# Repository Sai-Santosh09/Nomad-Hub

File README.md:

# NomadHub

NomadHub is a compact travel-inspired USB hub PCB designed in **KiCad**. It provides reliable USB connectivity through one USB Type-C upstream port, two USB Type-C downstream ports, and two USB Type-A downstream ports using the SL2.1S USB 2.0 Hub Controller.

## Features

- Compact travel-friendly PCB
- USB Type-C upstream port
- 2 × USB Type-C downstream ports
- 2 × USB Type-A downstream ports
- SL2.1S USB 2.0 Hub Controller
- 2-layer PCB design
- USB 2.0 compliant routing
- Gerber files included

## Images

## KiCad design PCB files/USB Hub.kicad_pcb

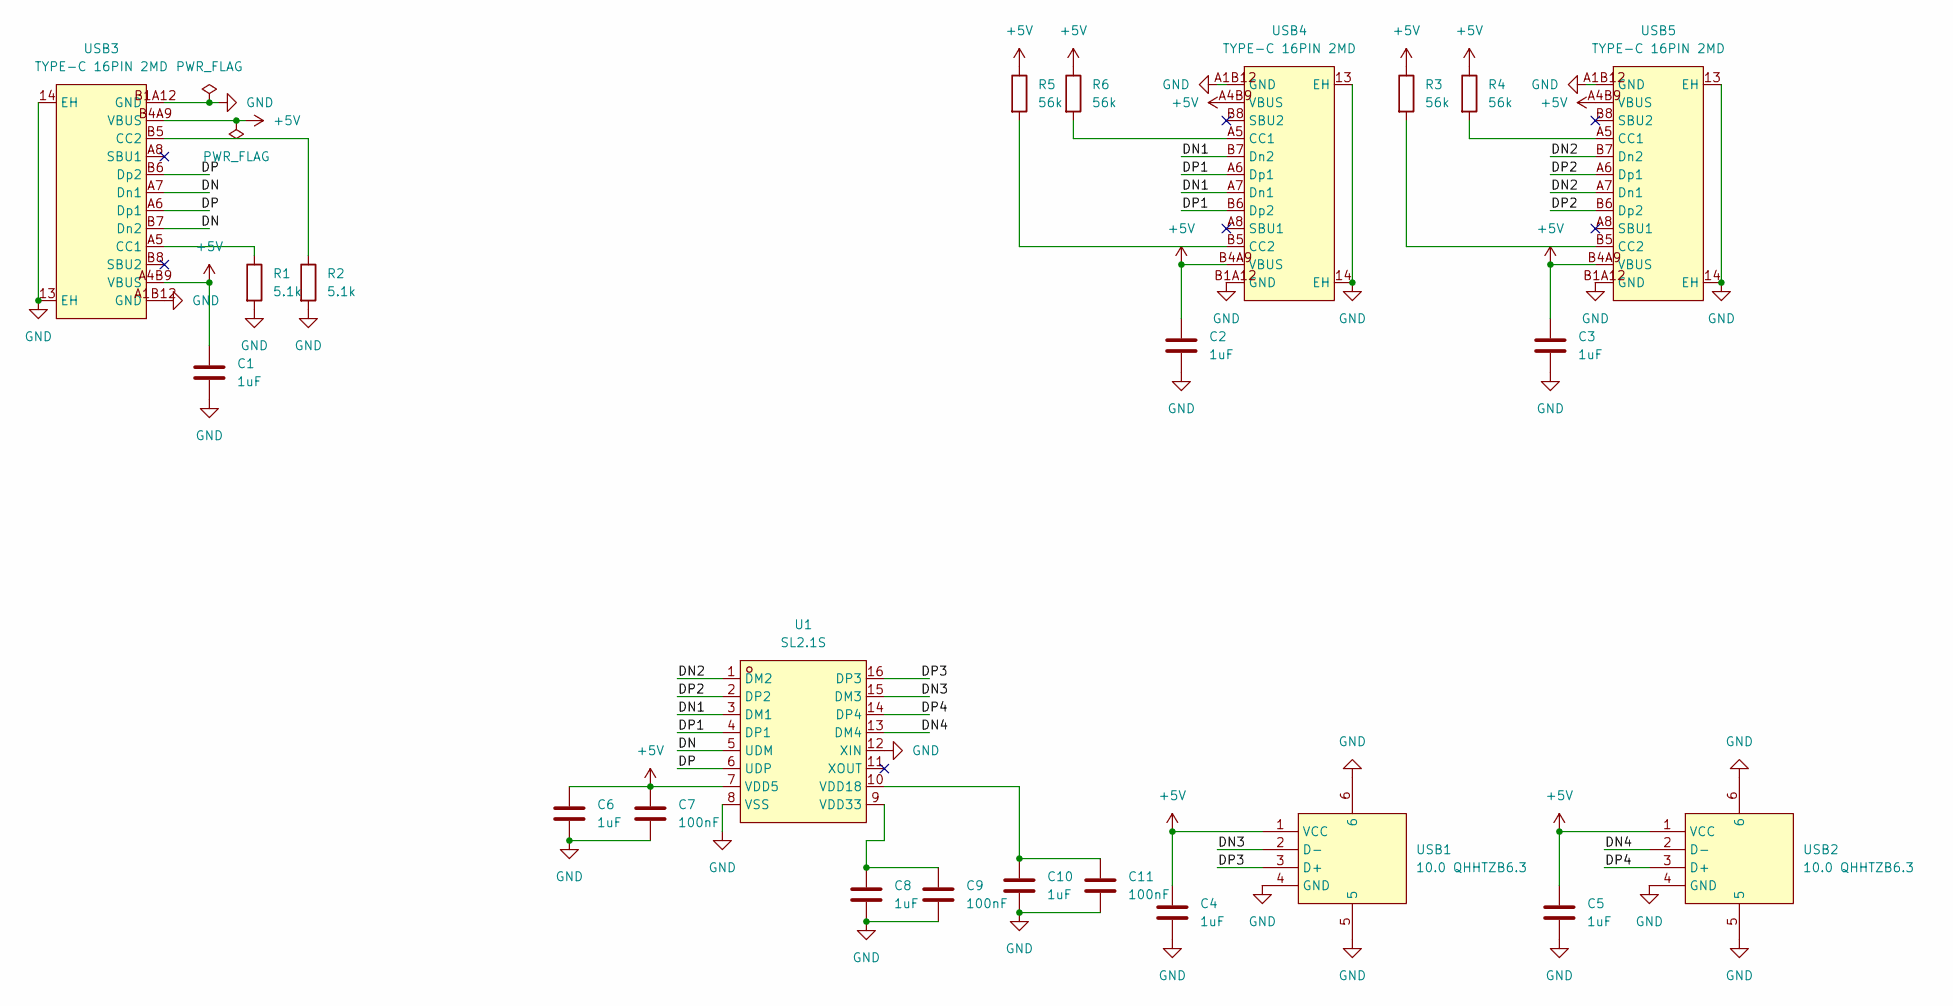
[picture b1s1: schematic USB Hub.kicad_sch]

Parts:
C1, C2, C3, C4, C5, C6, C8, C10: 1uF; C_0603_1608Metric
C7, C9, C11: 100nF; C_0603_1608Metric
R1, R2: 5.1k; R_0603_1608Metric
R3, R4, R5, R6: 56k; R_0603_1608Metric
U1: SL2.1S; SSOP-16_L4.6-W2.6-P0.53-LS4.0-BL; MPN SL2.1s; LCSC Part C2684433
USB1, USB2: 10.0 QHHTZB6.3; USB-A-TH_10.0QHHTZB6.3; MPN 10.0 QHHTZB6.3; LCSC Part C668591
USB3, USB4, USB5: TYPE-C 16PIN 2MD; USB-C-SMD_TYPE-C-16PIN-2MD-073; MPN TYPE-C 16PIN 2MD(073); LCSC Part C2765186

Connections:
+5V: C1.1, C2.1, C3.1, C4.1, C5.1, C6.1, C7.1, R3.1, R4.1, R5.1, R6.1, U1.7 (VDD5), USB1.1 (VCC), USB2.1 (VCC), USB3.A4B9 (VBUS), USB3.B4A9 (VBUS), USB4.A4B9 (VBUS), USB4.B4A9 (VBUS), USB5.A4B9 (VBUS), USB5.B4A9 (VBUS)
/DN: U1.5 (UDM), USB3.A7 (Dn1), USB3.B7 (Dn2)
/DN1: U1.3 (DM1), USB4.A7 (Dn1), USB4.B7 (Dn2)
/DN2: U1.1 (DM2), USB5.A7 (Dn1), USB5.B7 (Dn2)
/DN3: U1.15 (DM3), USB1.2 (D-)
/DN4: U1.13 (DM4), USB2.2 (D-)
/DP: U1.6 (UDP), USB3.A6 (Dp1), USB3.B6 (Dp2)
/DP1: U1.4 (DP1), USB4.A6 (Dp1), USB4.B6 (Dp2)
/DP2: U1.2 (DP2), USB5.A6 (Dp1), USB5.B6 (Dp2)
/DP3: U1.16 (DP3), USB1.3 (D+)
/DP4: U1.14 (DP4), USB2.3 (D+)
GND: C1.2, C2.2, C3.2, C4.2, C5.2, C6.2, C7.2, C8.2, C9.2, C10.2, C11.2, R1.2, R2.2, U1.8 (VSS), U1.12 (XIN), USB1.4 (GND), USB1.5, USB1.6, USB2.4 (GND), USB2.5, USB2.6, USB3.13 (EH), USB3.14 (EH), USB3.A1B12 (GND), USB3.B1A12 (GND), USB4.13 (EH), USB4.14 (EH), USB4.A1B12 (GND), USB4.B1A12 (GND), USB5.13 (EH), USB5.14 (EH), USB5.A1B12 (GND), USB5.B1A12 (GND)
unnamed: C10.1, C11.1, U1.10 (VDD18)
unnamed: C8.1, C9.1, U1.9 (VDD33)
unnamed: R1.1, USB3.A5 (CC1)
unnamed: R2.1, USB3.B5 (CC2)
unnamed: R6.2, USB4.A5 (CC1)
unnamed: R5.2, USB4.B5 (CC2)
unnamed: R4.2, USB5.A5 (CC1)
unnamed: R3.2, USB5.B5 (CC2)

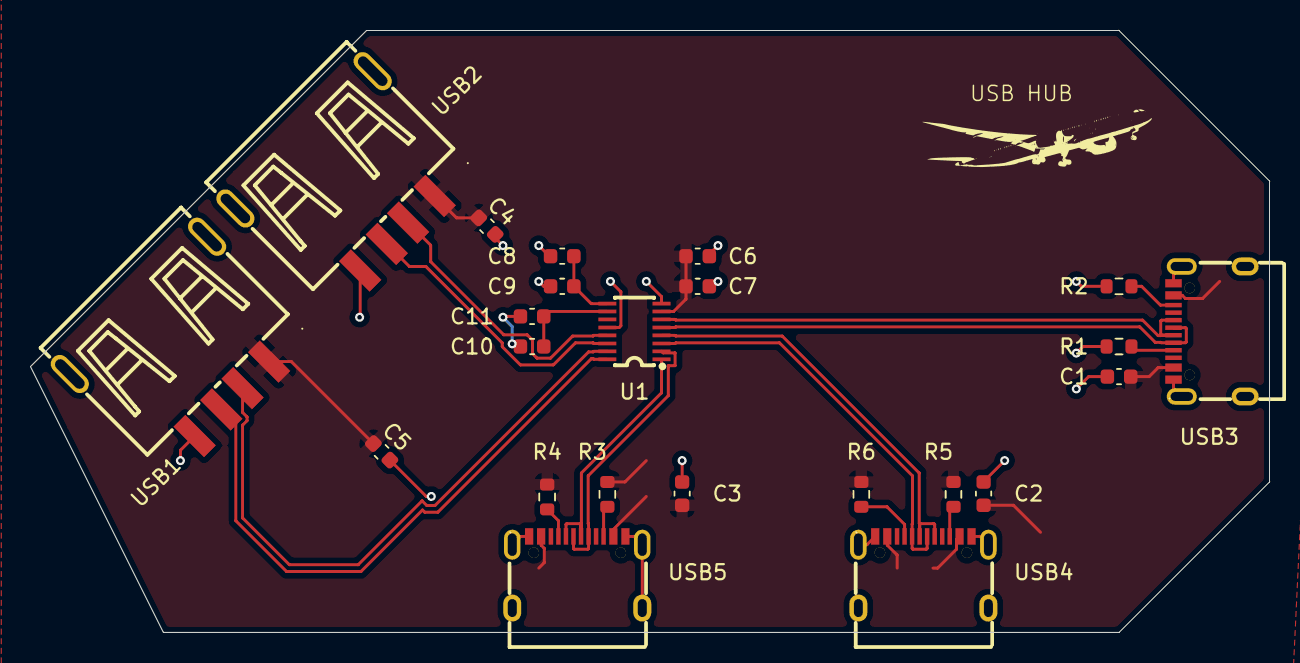
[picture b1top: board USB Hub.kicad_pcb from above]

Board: 2 copper layers, 82.3 x 40.0 mm, 23 parts (0 on the bottom side), 20 nets.

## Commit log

2026-06-27 USB Hub schematics and PCB files with gerber zip and step file and drl files
2026-06-27 updated the readme
2026-06-27 Final README
2026-06-29 Added images related to the project
